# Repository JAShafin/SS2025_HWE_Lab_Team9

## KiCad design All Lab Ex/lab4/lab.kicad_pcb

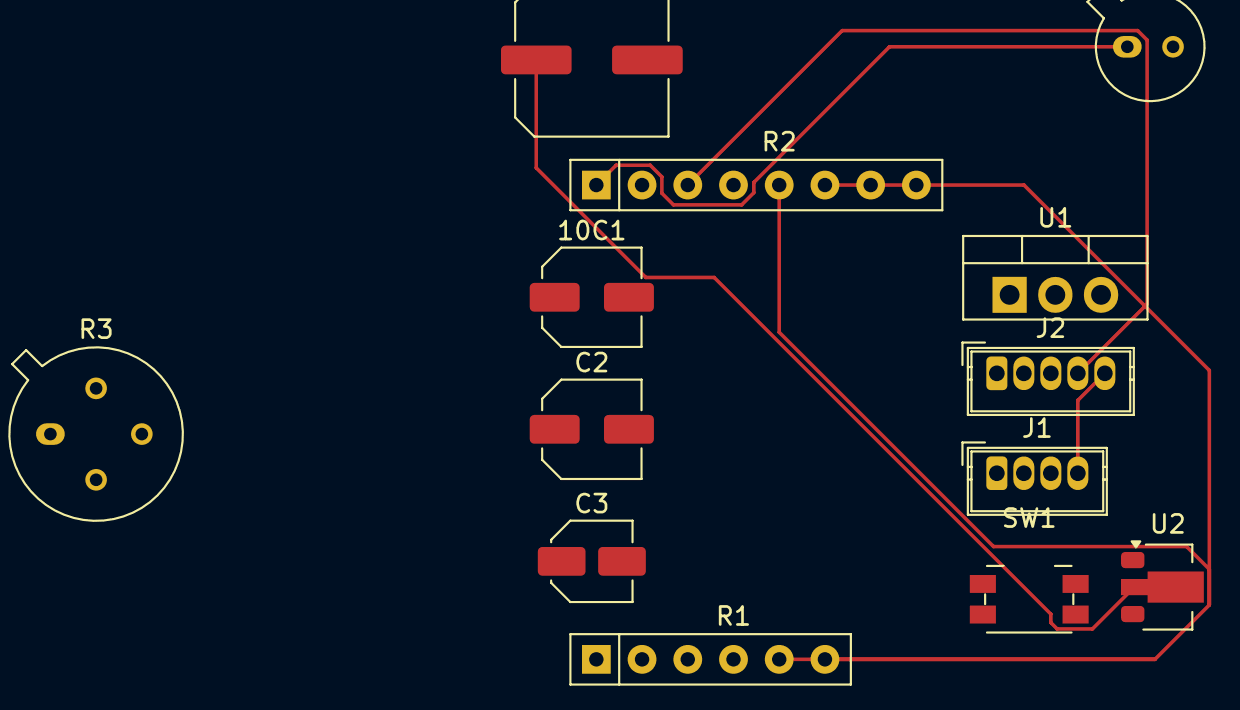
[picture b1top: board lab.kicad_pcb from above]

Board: 2 copper layers, 13 parts (0 on the bottom side), 8 nets.

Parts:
10C1: C; C_Elec_5x5.4
C2: C; C_Elec_5x5.8
C3: C; C_Elec_4x5.8
C4: C; C_Elec_8x6.2
D1: SFH480; TO-18-2_Window
J1: Barrel_Jack_Switch; Wuerth_WR-WTB_64800411622_1x04_P1.50mm_Vertical
J2: Conn_01x03_Pin; Wuerth_WR-WTB_64800511622_1x05_P1.50mm_Vertical
R1: R; R_Array_SIP6
R2: R; R_Array_SIP8
R3: R; TO-12-4
SW1: SW_SPST; Panasonic_EVQPUK_EVQPUB
U1: LM7805_TO220; TO-220-3_Vertical
U2: LM317L_SOT-89; SOT-89-3

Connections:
GND: 10C1.2, C2.2, C3.2, C4.2, J1.2, R1.2, U1.2 (GND)
unnamed: D1.2 (A), J2.3
unnamed: D1.1 (K), R2.1
unnamed: J1.1, SW1.1 (A)
unnamed: 10C1.1, C3.1, SW1.2 (B), U1.1 (VI), U2.3 (VI)
unnamed: C2.1, U1.3 (VO)
unnamed: R1.1, U2.1 (ADJ)
unnamed: C4.1, U2.2 (VO)

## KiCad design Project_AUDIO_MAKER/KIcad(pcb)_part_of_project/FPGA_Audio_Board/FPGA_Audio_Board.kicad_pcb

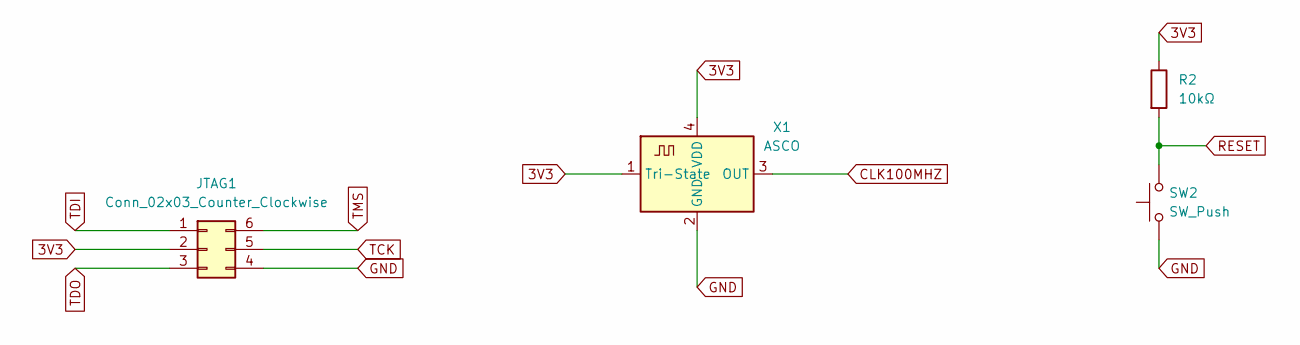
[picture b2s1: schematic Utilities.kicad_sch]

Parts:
JTAG1: Conn_02x03_Counter_Clockwise; PinHeader_2x03_P2.54mm_Vertical
R2: 10kΩ; R_0805_2012Metric
SW2: SW_Push; SW_PUSH_6mm_H5mm
X1: ASCO; Oscillator_SMD_Abracon_ASCO-4Pin_1.6x1.2mm

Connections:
3V3: JTAG1.2, R2.1, X1.1 (Tri-State), X1.4 (VDD); also elsewhere on the board
CLK100MHZ: X1.3 (OUT); also elsewhere on the board
GND: JTAG1.4, SW2.1, X1.2 (GND); also elsewhere on the board
RESET: R2.2, SW2.2; also elsewhere on the board
TCK: JTAG1.5; also elsewhere on the board
TDI: JTAG1.1; also elsewhere on the board
TDO: JTAG1.3; also elsewhere on the board
TMS: JTAG1.6; also elsewhere on the board

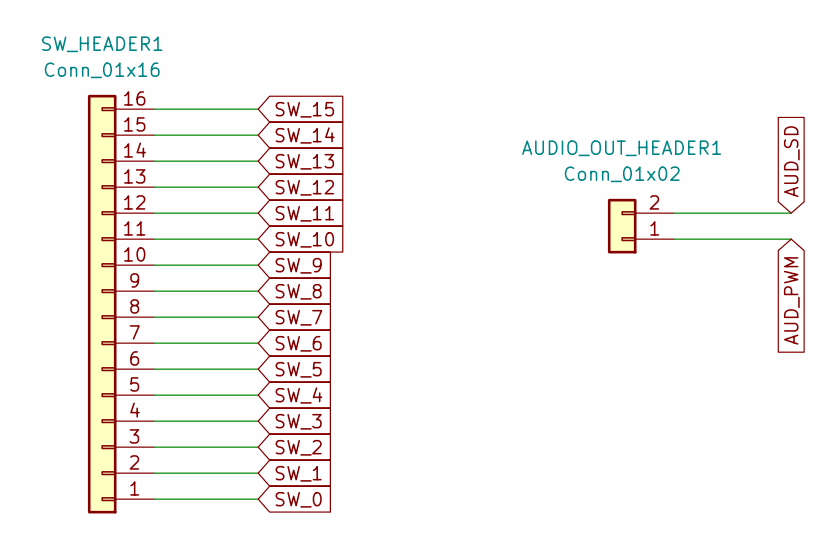
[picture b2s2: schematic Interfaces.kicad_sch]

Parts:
AUDIO_OUT_HEADER1: Conn_01x02; PinHeader_1x02_P2.54mm_Vertical
SW_HEADER1: Conn_01x16; PinHeader_1x16_P2.54mm_Vertical

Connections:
AUD_PWM: AUDIO_OUT_HEADER1.1; also elsewhere on the board
AUD_SD: AUDIO_OUT_HEADER1.2; also elsewhere on the board
SW_0: SW_HEADER1.1; also elsewhere on the board
SW_1: SW_HEADER1.2; also elsewhere on the board
SW_2: SW_HEADER1.3; also elsewhere on the board
SW_3: SW_HEADER1.4; also elsewhere on the board
SW_4: SW_HEADER1.5; also elsewhere on the board
SW_5: SW_HEADER1.6; also elsewhere on the board
SW_6: SW_HEADER1.7; also elsewhere on the board
SW_7: SW_HEADER1.8; also elsewhere on the board
SW_8: SW_HEADER1.9; also elsewhere on the board
SW_9: SW_HEADER1.10; also elsewhere on the board
SW_10: SW_HEADER1.11; also elsewhere on the board
SW_11: SW_HEADER1.12; also elsewhere on the board
SW_12: SW_HEADER1.13; also elsewhere on the board
SW_13: SW_HEADER1.14; also elsewhere on the board
SW_14: SW_HEADER1.15; also elsewhere on the board
SW_15: SW_HEADER1.16; also elsewhere on the board

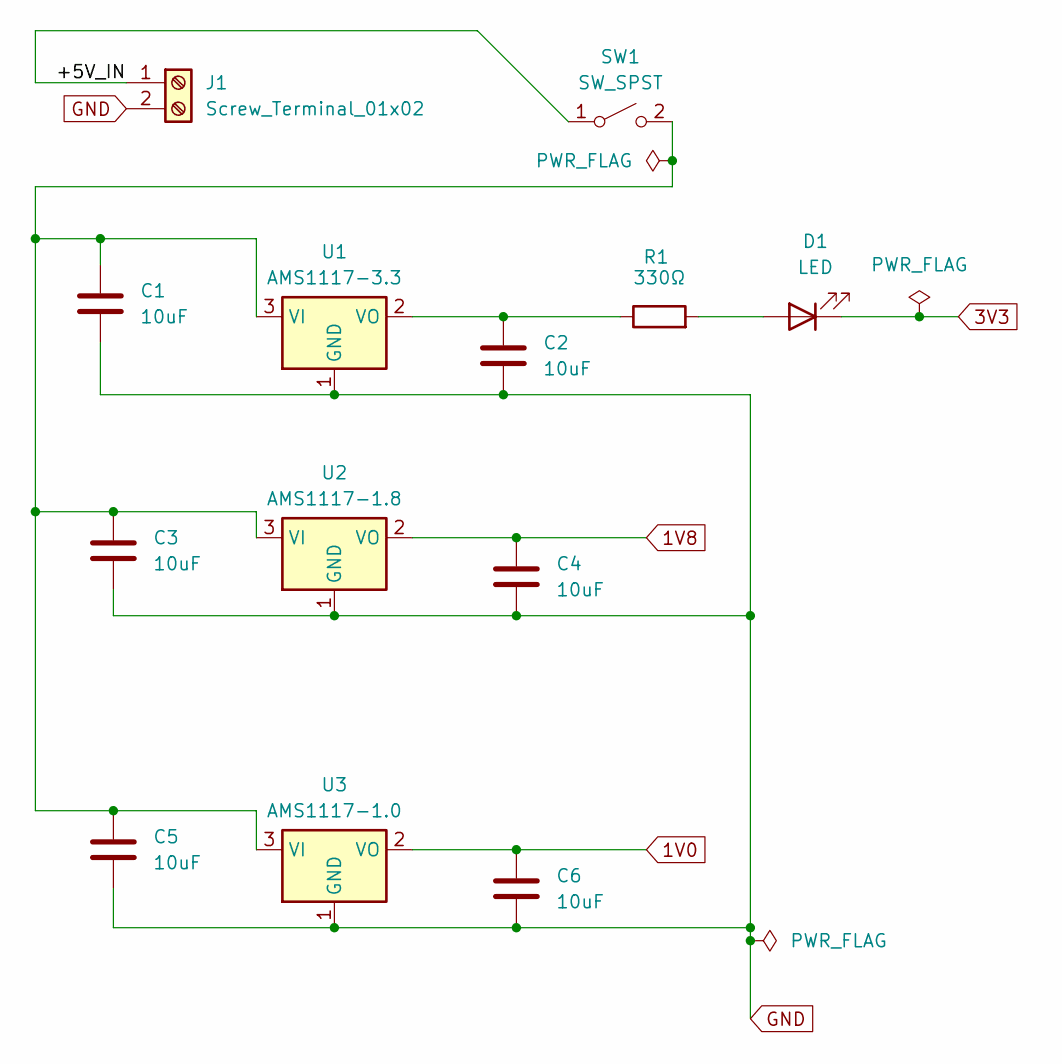
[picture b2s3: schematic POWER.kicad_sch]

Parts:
C1, C2, C3, C4, C5, C6: 10uF; C_0805_2012Metric
D1: LED; LED_0805_2012Metric
J1: Screw_Terminal_01x02; TerminalBlock_bornier-2_P5.08mm
R1: 330Ω; R_0805_2012Metric
SW1: SW_SPST; SW_PUSH_6mm_H5mm
U1: AMS1117-3.3; SOT-223-3_TabPin2
U2: AMS1117-1.8; SOT-223-3_TabPin2
U3: AMS1117-1.0; SOT-223-3_TabPin2

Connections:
1V0: C6.1, U3.2 (VO); also elsewhere on the board
1V8: C4.1, U2.2 (VO); also elsewhere on the board
3V3: D1.1 (K); also elsewhere on the board
/POWER/+5V_IN: J1.1, SW1.1 (A)
GND: C1.2, C2.2, C3.2, C4.2, C5.2, C6.2, J1.2, U1.1 (GND), U2.1 (GND), U3.1 (GND); also elsewhere on the board
unnamed: D1.2 (A), R1.2
unnamed: C1.1, C3.1, C5.1, SW1.2 (B), U1.3 (VI), U2.3 (VI), U3.3 (VI)
unnamed: C2.1, R1.1, U1.2 (VO)

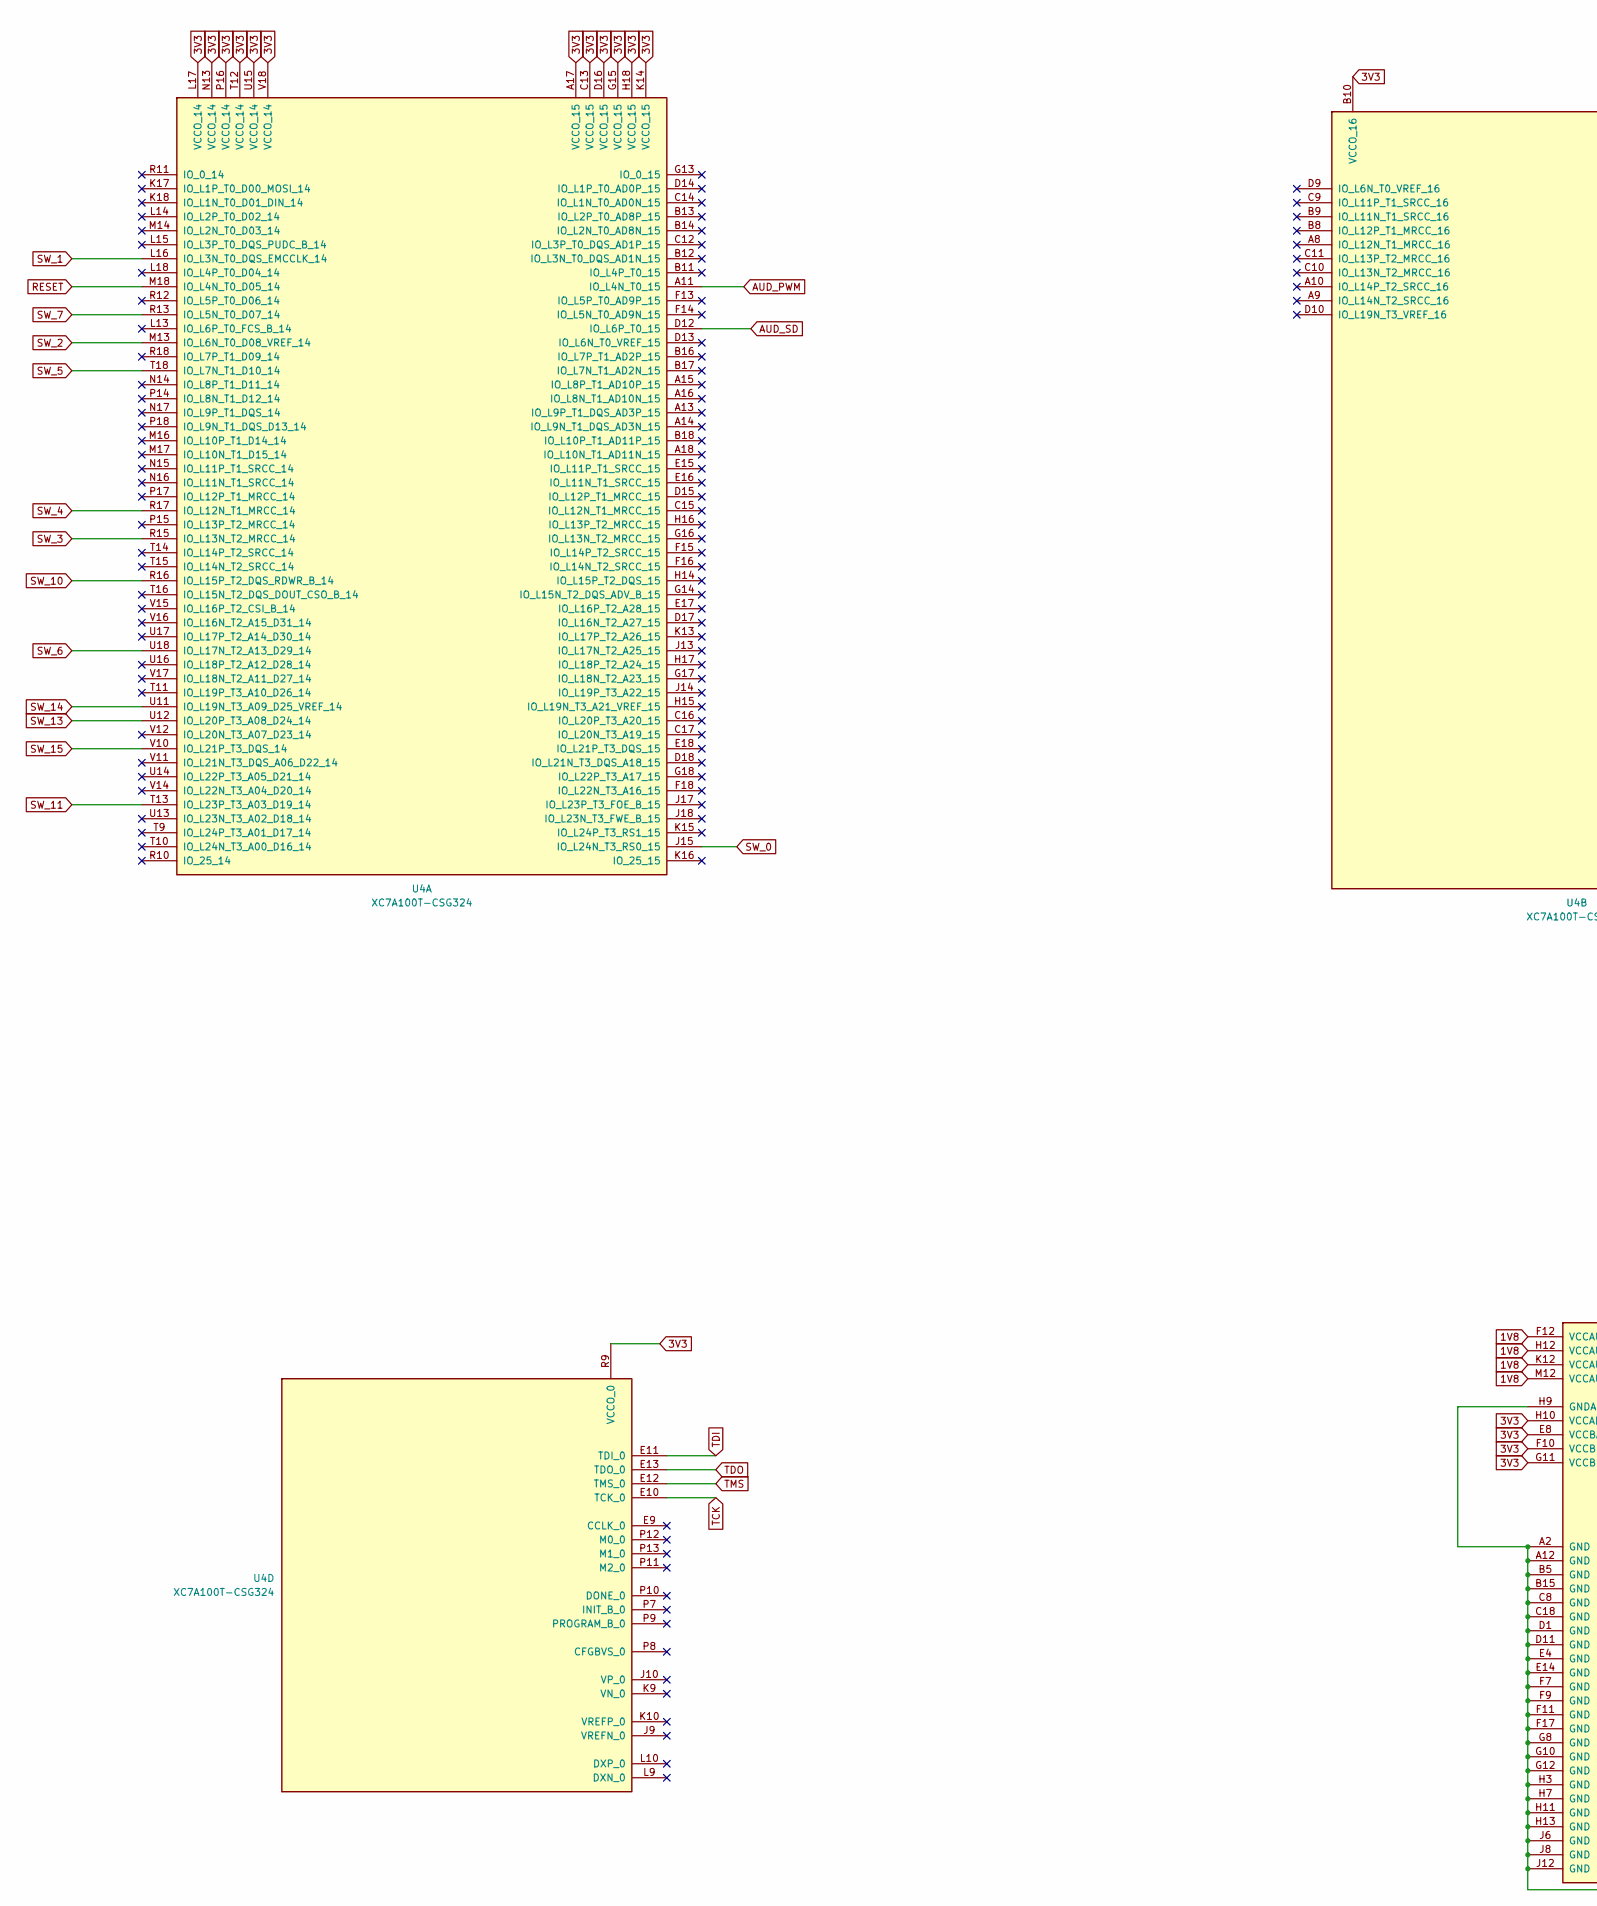
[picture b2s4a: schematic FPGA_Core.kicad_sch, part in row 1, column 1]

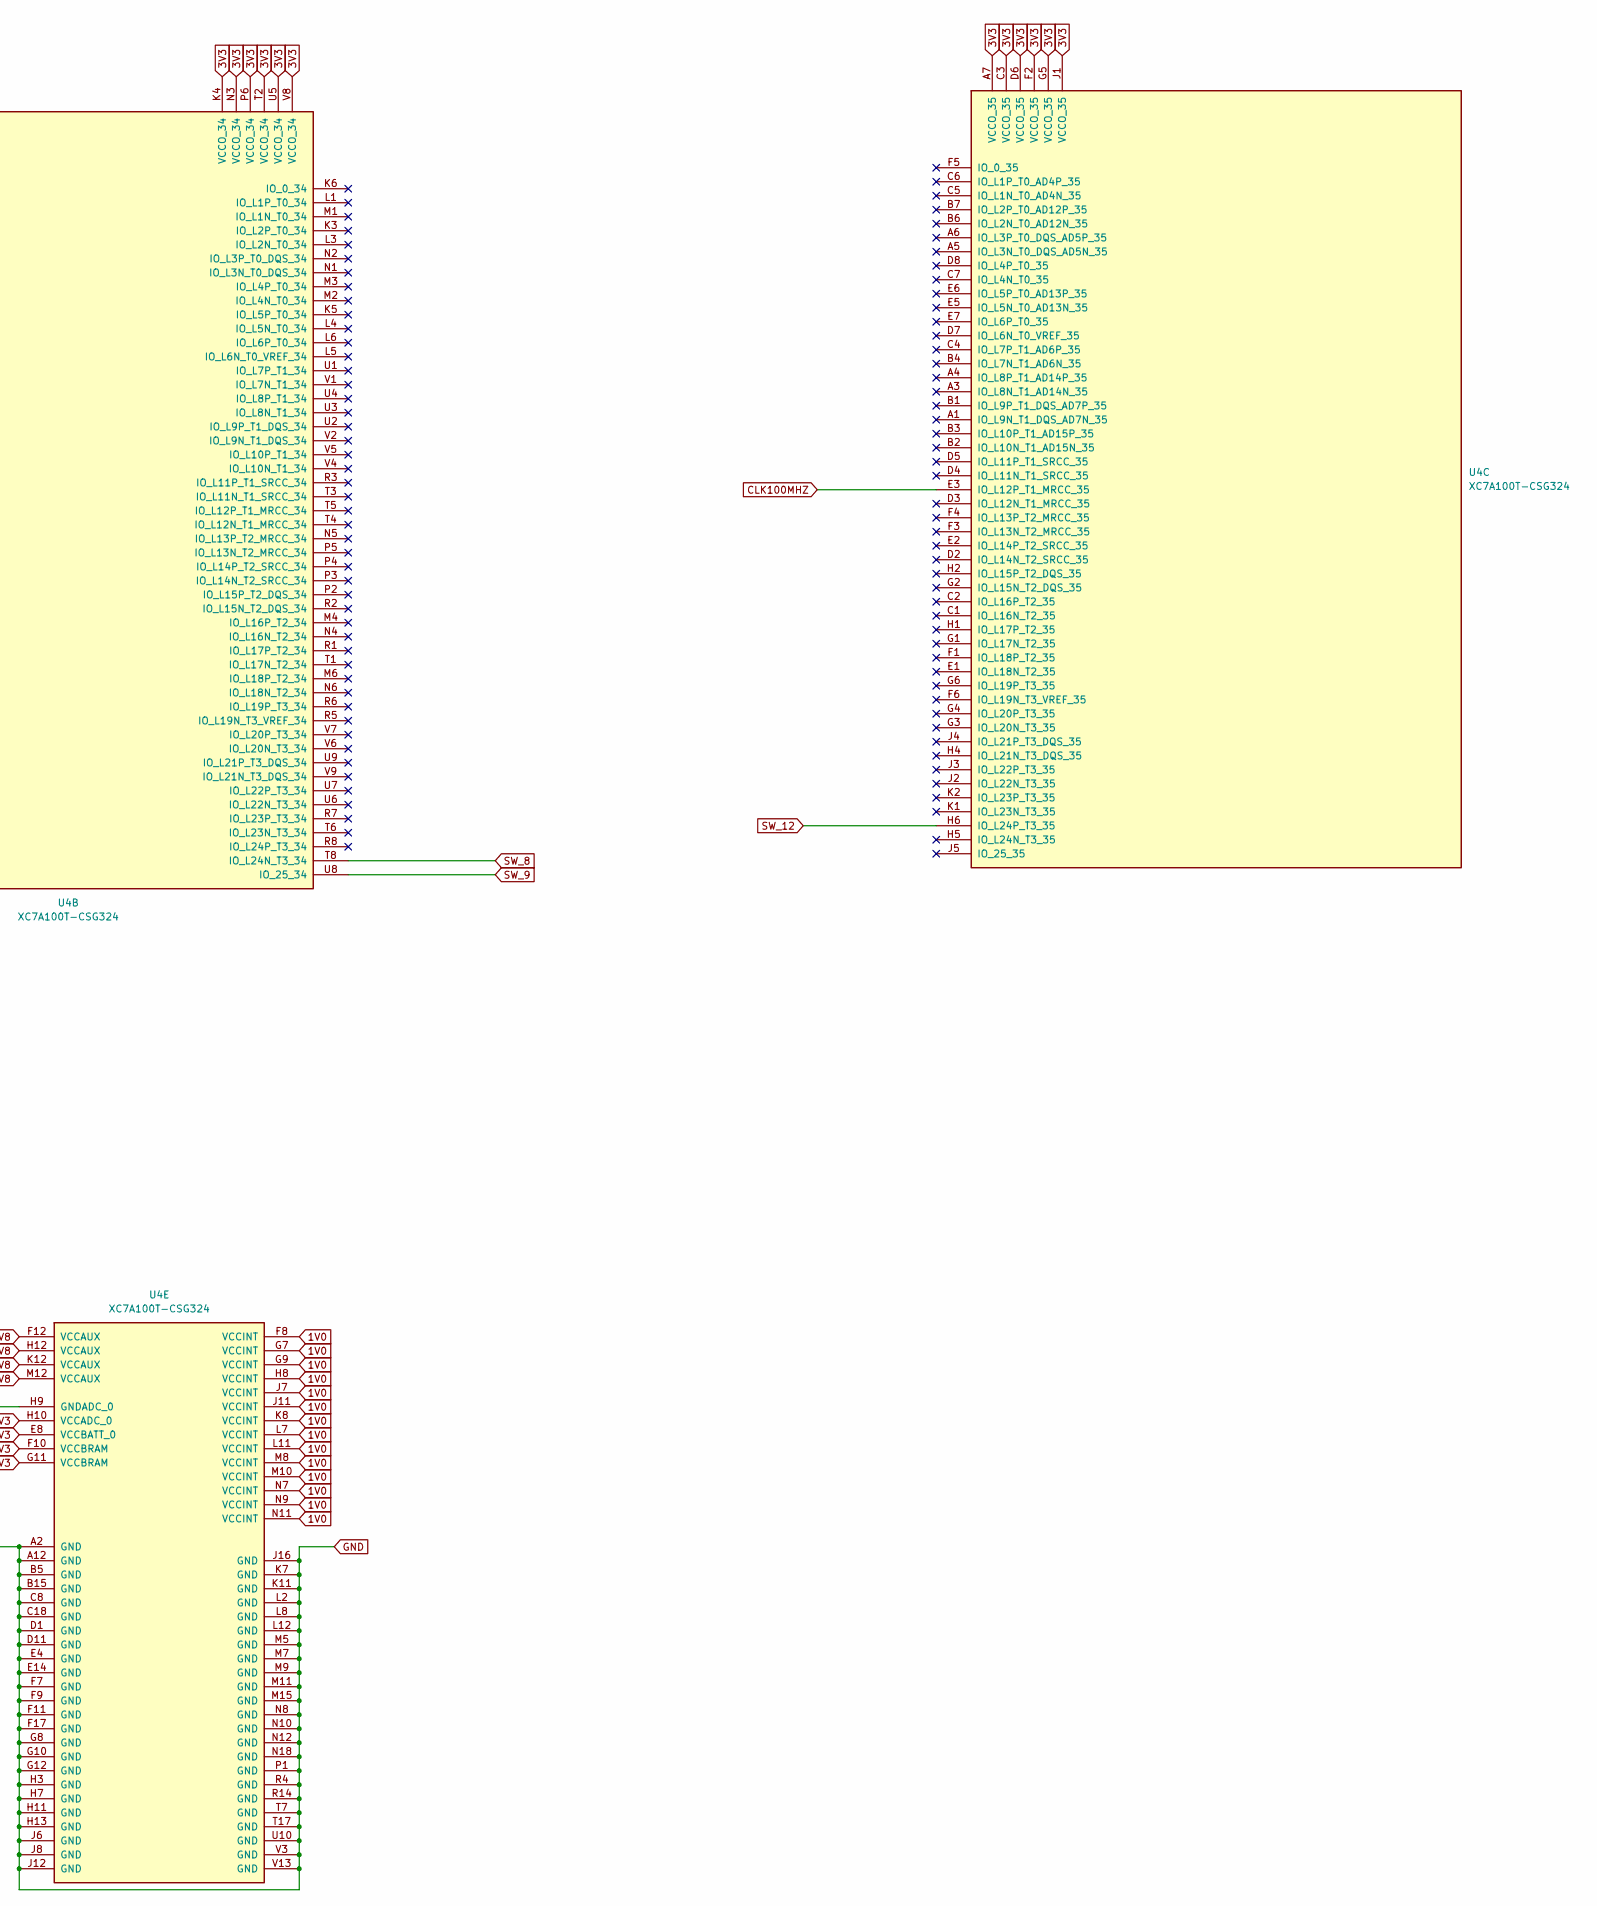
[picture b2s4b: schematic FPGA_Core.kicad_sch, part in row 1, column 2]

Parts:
U4: XC7A100T-CSG324; Xilinx_CSG324

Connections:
1V0: U4.F8 (VCCINT), U4.G7 (VCCINT), U4.G9 (VCCINT), U4.H8 (VCCINT), U4.J7 (VCCINT), U4.J11 (VCCINT), U4.K8 (VCCINT), U4.L7 (VCCINT), U4.L11 (VCCINT), U4.M8 (VCCINT), U4.M10 (VCCINT), U4.N7 (VCCINT), U4.N9 (VCCINT), U4.N11 (VCCINT); also elsewhere on the board
1V8: U4.F12 (VCCAUX), U4.H12 (VCCAUX), U4.K12 (VCCAUX), U4.M12 (VCCAUX); also elsewhere on the board
3V3: U4.A7 (VCCO_35), U4.A17 (VCCO_15), U4.B10 (VCCO_16), U4.C3 (VCCO_35), U4.C13 (VCCO_15), U4.D6 (VCCO_35), U4.D16 (VCCO_15), U4.E8 (VCCBATT_0), U4.F2 (VCCO_35), U4.F10 (VCCBRAM), U4.G5 (VCCO_35), U4.G11 (VCCBRAM), U4.G15 (VCCO_15), U4.H10 (VCCADC_0), U4.H18 (VCCO_15), U4.J1 (VCCO_35), U4.K4 (VCCO_34), U4.K14 (VCCO_15), U4.L17 (VCCO_14), U4.N3 (VCCO_34), U4.N13 (VCCO_14), U4.P6 (VCCO_34), U4.P16 (VCCO_14), U4.R9 (VCCO_0), U4.T2 (VCCO_34), U4.T12 (VCCO_14), U4.U5 (VCCO_34), U4.U15 (VCCO_14), U4.V8 (VCCO_34), U4.V18 (VCCO_14); also elsewhere on the board
AUD_PWM: U4.A11 (IO_L4N_T0_15); also elsewhere on the board
AUD_SD: U4.D12 (IO_L6P_T0_15); also elsewhere on the board
CLK100MHZ: U4.E3 (IO_L12P_T1_MRCC_35); also elsewhere on the board
GND: U4.A2 (GND), U4.A12 (GND), U4.B5 (GND), U4.B15 (GND), U4.C8 (GND), U4.C18 (GND), U4.D1 (GND), U4.D11 (GND), U4.E4 (GND), U4.E14 (GND), U4.F7 (GND), U4.F9 (GND), U4.F11 (GND), U4.F17 (GND), U4.G8 (GND), U4.G10 (GND), U4.G12 (GND), U4.H3 (GND), U4.H7 (GND), U4.H9 (GNDADC_0), U4.H11 (GND), U4.H13 (GND), U4.J6 (GND), U4.J8 (GND), U4.J12 (GND), U4.J16 (GND), U4.K7 (GND), U4.K11 (GND), U4.L2 (GND), U4.L8 (GND), U4.L12 (GND), U4.M5 (GND), U4.M7 (GND), U4.M9 (GND), U4.M11 (GND), U4.M15 (GND), U4.N8 (GND), U4.N10 (GND), U4.N12 (GND), U4.N18 (GND), U4.P1 (GND), U4.R4 (GND), U4.R14 (GND), U4.T7 (GND), U4.T17 (GND), U4.U10 (GND), U4.V3 (GND), U4.V13 (GND); also elsewhere on the board
RESET: U4.M18 (IO_L4N_T0_D05_14); also elsewhere on the board
SW_0: U4.J15 (IO_L24N_T3_RS0_15); also elsewhere on the board
SW_1: U4.L16 (IO_L3N_T0_DQS_EMCCLK_14); also elsewhere on the board
SW_2: U4.M13 (IO_L6N_T0_D08_VREF_14); also elsewhere on the board
SW_3: U4.R15 (IO_L13N_T2_MRCC_14); also elsewhere on the board
SW_4: U4.R17 (IO_L12N_T1_MRCC_14); also elsewhere on the board
SW_5: U4.T18 (IO_L7N_T1_D10_14); also elsewhere on the board
SW_6: U4.U18 (IO_L17N_T2_A13_D29_14); also elsewhere on the board
SW_7: U4.R13 (IO_L5N_T0_D07_14); also elsewhere on the board
SW_8: U4.T8 (IO_L24N_T3_34); also elsewhere on the board
SW_9: U4.U8 (IO_25_34); also elsewhere on the board
SW_10: U4.R16 (IO_L15P_T2_DQS_RDWR_B_14); also elsewhere on the board
SW_11: U4.T13 (IO_L23P_T3_A03_D19_14); also elsewhere on the board
SW_12: U4.H6 (IO_L24P_T3_35); also elsewhere on the board
SW_13: U4.U12 (IO_L20P_T3_A08_D24_14); also elsewhere on the board
SW_14: U4.U11 (IO_L19N_T3_A09_D25_VREF_14); also elsewhere on the board
SW_15: U4.V10 (IO_L21P_T3_DQS_14); also elsewhere on the board
TCK: U4.E10 (TCK_0); also elsewhere on the board
TDI: U4.E11 (TDI_0); also elsewhere on the board
TDO: U4.E13 (TDO_0); also elsewhere on the board
TMS: U4.E12 (TMS_0); also elsewhere on the board

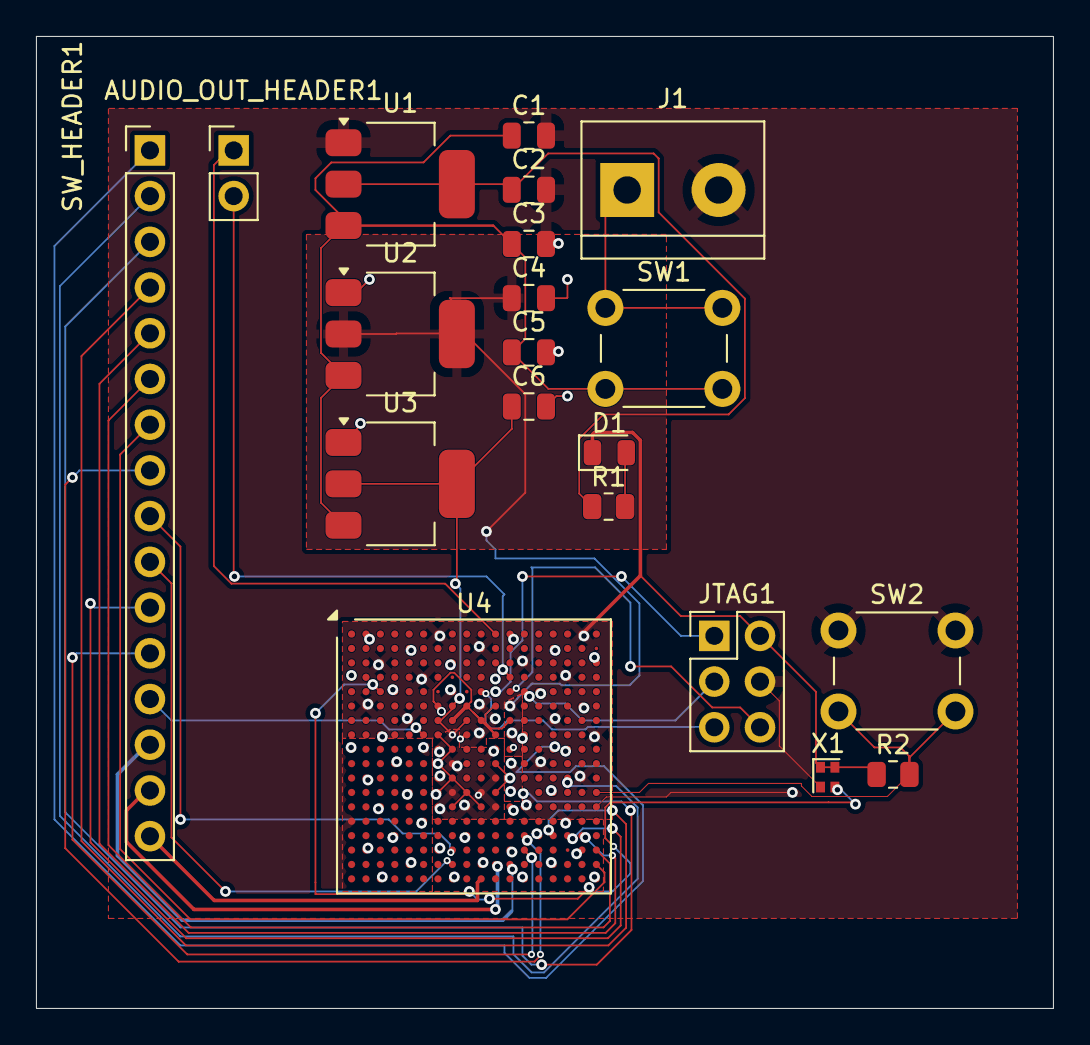
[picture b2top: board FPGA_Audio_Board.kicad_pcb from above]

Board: 4 copper layers, 56.5 x 54.0 mm, 20 parts (0 on the bottom side), 32 nets.

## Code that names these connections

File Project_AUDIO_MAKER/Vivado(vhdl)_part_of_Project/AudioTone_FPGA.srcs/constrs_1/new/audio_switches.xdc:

# Clock
set_property -dict { PACKAGE_PIN E3 IOSTANDARD LVCMOS33 } [get_ports { CLK100MHZ }]
create_clock -name sys_clk -period 10.00 [get_ports { CLK100MHZ }]

# Reset button (now from M18)
set_property -dict { PACKAGE_PIN M18 IOSTANDARD LVCMOS33 } [get_ports { RESET }]

# Switches
set_property -dict { PACKAGE_PIN J15 IOSTANDARD LVCMOS33 } [get_ports { SW[0] }]
set_property -dict { PACKAGE_PIN L16 IOSTANDARD LVCMOS33 } [get_ports { SW[1] }]
set_property -dict { PACKAGE_PIN M13 IOSTANDARD LVCMOS33 } [get_ports { SW[2] }]
set_property -dict { PACKAGE_PIN R15 IOSTANDARD LVCMOS33 } [get_ports { SW[3] }]
set_property -dict { PACKAGE_PIN R17 IOSTANDARD LVCMOS33 } [get_ports { SW[4] }]
set_property -dict { PACKAGE_PIN T18 IOSTANDARD LVCMOS33 } [get_ports { SW[5] }]
set_property -dict { PACKAGE_PIN U18 IOSTANDARD LVCMOS33 } [get_ports { SW[6] }]
set_property -dict { PACKAGE_PIN R13 IOSTANDARD LVCMOS33 } [get_ports { SW[7] }]
set_property -dict { PACKAGE_PIN T8  IOSTANDARD LVCMOS33 } [get_ports { SW[8] }]
set_property -dict { PACKAGE_PIN U8  IOSTANDARD LVCMOS33 } [get_ports { SW[9] }]
set_property -dict { PACKAGE_PIN R16 IOSTANDARD LVCMOS33 } [get_ports { SW[10] }]
set_property -dict { PACKAGE_PIN T13 IOSTANDARD LVCMOS33 } [get_ports { SW[11] }]
set_property -dict { PACKAGE_PIN H6  IOSTANDARD LVCMOS33 } [get_ports { SW[12] }]
set_property -dict { PACKAGE_PIN U12 IOSTANDARD LVCMOS33 } [get_ports { SW[13] }]
set_property -dict { PACKAGE_PIN U11 IOSTANDARD LVCMOS33 } [get_ports { SW[14] }]
set_property -dict { PACKAGE_PIN V10 IOSTANDARD LVCMOS33 } [get_ports { SW[15] }]

# Audio Output
set_property -dict { PACKAGE_PIN A11 IOSTANDARD LVCMOS33 } [get_ports { AUD_PWM }]
set_property -dict { PACKAGE_PIN D12 IOSTANDARD LVCMOS33 } [get_ports { AUD_SD }]

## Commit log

2025-04-09 Add lab1 with ex1 to ex4 folders
2025-04-09 Remove work folder
2025-04-09 Updated files in lab1 project
2025-04-09 Your commit message
2025-04-09 Sync latest changes from PC
2025-06-14 Added new files
2025-06-14 Updated PCB files, added PDFs, Gerbers, STEP, and deleted old backups
2025-07-13 Update KiCad project files
2025-07-13 Mirror PC folder: add All Lab Ex and remove old files
2025-07-13 Update with latest changes from PC
